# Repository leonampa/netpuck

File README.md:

# **NetPuck 5G: A Specialized 5GHz Wireless & Network Auditor**

----------

# 🗃️ This project has been archived.
**9th May:** It’s been 30 days since my latest ticket to Support, and over five weeks since the last human feedback. At this point, the project has shifted from a fun hardware challenge into a lingering chore on my to-do list. The educational ROI has hit its limit - I’ve already learned what I came for: Fusion 360, KiCad, etc. Since the program has stalled on the administrative side, I’m officially archiving the NetPuck to clear my headspace for projects that actually move forward. 

----------

# **0\. Introduction**

The NetPuck 5G is a handheld device, purpose-built to connect the worlds of software-driven network diagnostics and hardware-focused wireless analysis.

Made on Hack Club Blueprint 🚩- [https://blueprint.hackclub.com/projects/13740](https://blueprint.hackclub.com/projects/13740)

## **0.1 Why did I build this?**

* **I needed a network auditing device.** As a beginner IT Support Technician, I have a vast variety of tools for every job, but I've been lacking tools (and knowledge) regarding networking infrastructure. I've been making do with my phone and generic, no-brand WiFi strength scanning applications on my phone, but that is just not reliable for my purpose.  
* **I wanted to learn about hardware engineering.** I've always been interested in the “guts” of the devices around me. From a very young age, with a screwdriver in hand, I started taking devices that would otherwise be trashed apart, curious to see what makes them work. A few months ago, I also bought a soldering iron, and learned the skill of soldering and desoldering. In my curious journey of hardware engineering, the next step would be designing and having a custom PCB made.  
* **I wanted something to showcase in my portfolio.** Projects and contributions are largely important factors in one's portfolio, especially at an age where they cannot work, like me. I wanted to enrich my portfolio with personal projects, and Hack Club’s blueprint was the perfect, guided opportunity for me to do so.

## **0.2 What is it made of?**

It uses:

* the Waveshare ESP32-S3 Pico, as the main processing unit for the entire device  
* a BW16, solely for Access Point scanning, thanks to its 5GHz capabilities   
* a W5500 Ethernet module, for listing details about the network it is connected to  
* a 1.8’ inch LCD module, for providing all information gathered from the aforementioned boards to the user  
* a low-profile 5-way digital navigation joystick, for navigating the menus of the device  
* a MH-CD42 charging and boost-up module and two Samsung 18650 batteries, for powering the device from batteries, reliably.

## **0.3 So, what does it do?**

The NetPuck 5G has two functions; Wireless Access Point strength scanning, and Wired Network details.

* Wireless Access Point strength scanning  
  * This function uses the BW16, which communicates with the ESP32 via UART to list all 2.4GHz and 5GHz Access Points within reach, and the strength of each one, measured in dBm.  
* LAN details  
  * This function detects specific details about the network the W5500 module is plugged into. Specifically: ICMP Echo to 8.8.8.8, Gateway IP (from DHCP Lease), ICMP Echo to Gateway (Confirms local LAN integrity), LLDP (Passive sniff for Link Layer Discovery Protocol packets), Reverse DNS lookup of the Gateway’s Public IP, Gateway Domain Name (from DHCP Option 15), NLA Information, Gateway MAC (ARP-resolved)

# **1\. Pinout**

Grounds not listed; all grounds connect to each other  
The Pin/As/To/For tables are read as: The Pin \[Pin\] functions as/is labeled as \[As\], and goes to pin \[To\], (and is used) for \[For\].   

## **1.1 ESP32-S3**

| Pin | As | To | For |
| :---- | :---- | :---- | :---- |
| Vbus/40 | \+5V | MH-CD42 @ 5V OUT | Powering the ESP |
| GP5/27 | LCD\_BL | LCD @ BL | Controlling the backlight |
| GP6/29 | W5500\_RST | W5500 @ RST | Resetting the W5500 |
| GP7/31 | LCD\_RST | LCD @ RST | LCD’s Resetting the LCD |
| GP8/32 | LCD\_DC | LCD @ DC | Data/Command |
| GP9/33 | W5500\_CS | W5500 @ CS | W5500’s SPI Chip Select  |
| GP10/34 | LCD\_CS | LCD @ CS | LCD’s SPI Chip Select |
| 3V3/36 | 3V3 | LCD @ VCC, W5500 @ V | Powering the LCD and W5500 |
| GP11/1 | SPI\_MOSI | LCD @ DIN, W5500 @ MO | Transferring data via SPI from the ESP32 (Master), to the LCD and W5500 (Slaves) |
| GP12/2 | SPI\_SCK | LCD @ CLK, W5500 @ SCK | Serial Clock for SPI |
| GP13/4 | SPI\_MISO | W5500 @ MI | Transferring data via SPI from the W5500 (Slave) to the ESP32 (Master) |
| GP14/5 | BW16\_EN | BW16 @ EN | BW16’s Enable Pin |
| GP17/9 | BW16\_RX | BW16 @ 7 | UART (ESP32 → BW16) |
| GP18/10 | BW16\_TX | BW16 @ 8 | UART (ESP32 ← BW16) |
| GP34/12 | MID | STICK @ MID | Joystick’s Click |
| GP35/14 | UP | STICK @ UP | Joystick’s Up |
| GP36/15 | DOWN | STICK @ DOWN | Joystick’s Down |
| GP37/16 | LEFT | STICK @ LEFT | Joystick’s Left |
| GP38/17 | RIGHT | STICK @ RIGHT | Joystick’s Right |

## **1.2 BW16**

| Pin | As | To | For |
| :---- | :---- | :---- | :---- |
| 5V | \+5V | MH-CD42 @ 5V OUT | Powering the BW16 |
| PA7/TX | BW16\_TX | ESP @ GP17/9 | UART (ESP32 ← BW16) |
| PA8/RX | BW16\_RX | ESP @ GP18/10 | UART (ESP32 → BW16) |
| EN | BW16\_EN | ESP @ GP14/5 | Enable Pin |

## **1.3 W5500**

| Pin | As | To | For |
| :---- | :---- | :---- | :---- |
| RST | W5500\_RST | ESP @ GP6/29 | Resetting the W5500 |
| CS | W5500\_CS | ESP @ GP9/34 | W5500’s SPI Chip Select  |
| V | 3V3 | ESP @ 3V3 | Powering the LCD and W5500 |
| SCK | SPI\_SCK | ESP @ GP12/2 | Serial Clock for SPI |
| MI | SPI\_MISO | ESP @ GP13/4 | Transferring data via SPI from the W5500 (Slave) to the ESP32 (Master) |
| MO | SPI\_MOSI | ESP @ GP11/1 | Transferring data via SPI from the ESP32 (Master), to theW5500 (Slave) |

## **1.4 LCD**

| Pin | As | To | For |
| :---- | :---- | :---- | :---- |
| BL  | LCD\_BL | ESP @ GP5/27 | Controlling the backlight |
| RST  | LCD\_RST | ESP @ GP7/31 | Resetting the LCD |
| DC  | LCD\_DC | ESP @ GP8/32 | LCD’s Data/Command |
| CS  | LCD\_CS | ESP @ GP10/34 | LCD’s SPI Chip Select |
| VCC  | 3V3 | ESP @ 3V3/36 | Powering the LCD |
| DIN  | SPI\_MOSI | ESP @ GP11/1 | Transferring data via SPI from the ESP32 (Master), to the LCD (Slave) |
| CLK  | SPI\_SCK | ESP @ GP12/2 | Serial Clock for SPI |

## **1.5 Joystick** 

| Pin | As | To | For |
| :---- | :---- | :---- | :---- |
| MID | MID | ESP @ GP34/12 | Joystick’s Click |
| UP | UP | ESP @ GP35/14 | Joystick’s Up |
| DOWN | DOWN | ESP @ GP36/15 | Joystick’s Down |
| LEFT | LEFT | ESP @ GP37/16 | Joystick’s Left |
| RIGHT | RIGHT | ESP @ GP38/17 | Joystick’s Right |

## **1.6 MH-CD42 Charging Module**

| Pin | As | To | For |
| :---- | :---- | :---- | :---- |
| 5V OUT | \+5V | ESP @ Vbus/40, BW16 @ 5V | Powering the ESP and BW16 |
| VIN  | VUSB | USB @ V | Powering the MH-CD42 |
| BAT | VBAT | (external batteries) | Powering the MH-CD42 |

## **1.7 USB Port**

| Pin | As | To | For |
| :---- | :---- | :---- | :---- |
| V | VUSB | VIN | Powering the MH-CD42 |

# **2\. PCB**

I used KiCad to design the PCB. Through a few struggles (as described on Journal), I landed on this design:

# **3\. Case**

I used Autodesk Fusion to make the case (as described on Journal). The enclosure is designed for field durability, featuring a 'Sandwich Mount' architecture. It utilizes M3 heat-set inserts and M3 Nylon screws, instead of Stainless Steel, to avoid signal interference.

# **4\. Bill Of Materials**

| Item | €/pcs | Qty | € Total | Link |
| :---- | ----- | ----- | ----- | :---- |
| **GRobotronics** |  |  |  |  |
| eSUN PETG+HS 1.75mm 1kg \- Solid Black | €19.90 | 1 | €19.90 | [https://grobotronics.com/esun-petghs-1-75mm-1kg-solid-black.html](https://grobotronics.com/esun-petghs-1-75mm-1kg-solid-black.html) |
| Soldering Wire Brofil 60 100g 1mm | €7.20 | 1 | €7.20 | [https://grobotronics.com/soldering-wire-brofil-60-100g-1mm.html](https://grobotronics.com/soldering-wire-brofil-60-100g-1mm.html) |
| Waveshare ESP32-S3 Pico With Pre-soldered Headers | €13.60 | 1 | €13.60 | [https://grobotronics.com/waveshare-esp32-s3-development-board.html?variation\_id=18355](https://grobotronics.com/waveshare-esp32-s3-development-board.html?variation_id=18355) |
| Battery Lithium 18650 3.6V 3400mAh \- Samsung INR18650-35E | €5.80 | 2 | €11.60 | [https://grobotronics.com/battery-lithium-18650-3.6v-3400mah-8a-samsung-inr18650-35e.html](https://grobotronics.com/battery-lithium-18650-3.6v-3400mah-8a-samsung-inr18650-35e.html) |
| Battery Holder 2x18650 \- with Wires & Switch | €1.20 | 1 | €1.20 | [https://grobotronics.com/battery-lithium-18650-3.6v-3400mah-8a-samsung-inr18650-35e.html](https://grobotronics.com/battery-lithium-18650-3.6v-3400mah-8a-samsung-inr18650-35e.html) |
| Joystick Module 5-Way | €2.60 | 1 | €2.60 | [https://grobotronics.com/5-way-joystick-module.html](https://grobotronics.com/5-way-joystick-module.html) |
| Waveshare LCD 1.8" 128×160 SPI | €11.20 | 1 | €11.20 | [https://grobotronics.com/display-1.8-128x160-lcd-module.html](https://grobotronics.com/display-1.8-128x160-lcd-module.html) |
| USB Type-C Breakout Board \- Straight Header | €0.80 | 1 | €0.80 | [https://grobotronics.com/usb-type-c-breakout-board-straight-header.html](https://grobotronics.com/usb-type-c-breakout-board-straight-header.html) |
| Pin Header 1x40 Male 2.54 mm Black | €0.10 | 1 | €0.10 | [https://grobotronics.com/pin-header-1x40-male-2.54-mm-black.html](https://grobotronics.com/pin-header-1x40-male-2.54-mm-black.html) |
| Pin Header 1x10 Female 2.54mm | €0.17 | 4 | €0.68 | [https://grobotronics.com/pin-header-1x10-female-2.54mm.html](https://grobotronics.com/pin-header-1x10-female-2.54mm.html) |
| Pin Header 1x8 Female 2.54mm | €0.10 | 3 | €0.30 | [https://grobotronics.com/pin-header-1x8-female-2.54mm.html](https://grobotronics.com/pin-header-1x8-female-2.54mm.html) |
| Arduino Long Header 8pins | €0.25 | 1 | €0.25 | [https://grobotronics.com/arduino-long-header-8pins.html](https://grobotronics.com/arduino-long-header-8pins.html) |
| Pin Header Female 1x6 2.54mm | €0.08 | 3 | €0.24 | [https://grobotronics.com/pin-header-1x6-female-2.54mm.html](https://grobotronics.com/pin-header-1x6-female-2.54mm.html) |
| Pin Header 1x4 Long Stackable | €0.20 | 1 | €0.20 | [https://grobotronics.com/pin-header-1x4-long-stackable.html](https://grobotronics.com/pin-header-1x4-long-stackable.html) |
| Threaded Insert M3 \- 5.7x4.6mm | €0.15 | 10 | €1.50 | [https://grobotronics.com/threaded-insert-m3-short-3x4-6.html](https://grobotronics.com/threaded-insert-m3-short-3x4-6.html) |
| Bolt M3 \- Nylon (20mm) | €0.30 | 10 | €3.00 | [https://grobotronics.com/m3.html?variation\_id=12363](https://grobotronics.com/m3.html?variation_id=12363) |
| High Temperature Adhesive Tape 50mm \- 33m | €7.90 | 1 | €7.90 | [https://grobotronics.com/high-temperature-adhesive-tape-50mm-33m.html](https://grobotronics.com/high-temperature-adhesive-tape-50mm-33m.html) |
| YATO YT-2081 Side Cutting Pliers 115mm | €3.60 | 1 | €3.60 | [https://grobotronics.com/yato-cutting-pliers-115mm.html](https://grobotronics.com/yato-cutting-pliers-115mm.html) |
| Shipping (BOXNOW) | €0.00 | 0 | €0.00 |  |
| **Subtotal** |  | 44 | €85.87 |  |
|  |  |  |  |  |
| **AliExpress** |  |  |  |  |
| Dual-band WiFi \+ Bluetooth 5.0 IoT Core Board (BW16 RTL8720DN) Suitable for Arduino and Smart Home Projects (IPEX Antenna) | €7.24 | 1 | €9.52 | [https://www.aliexpress.com/item/1005010064459718.html?spm=a2g0o.detail.0.0.7236U0QJU0QJSg\&mp=1\&pdp\_npi=6%40dis%21EUR%21EUR%209.55%21EUR%201.95%21%21EUR%201.95%21%21%21%402103835e17741877141951141e5be7%2112000051007214201%21ct%21GR%21-1%21%211%210%21](https://www.aliexpress.com/item/1005010064459718.html?spm=a2g0o.detail.0.0.7236U0QJU0QJSg&mp=1&pdp_npi=6%40dis%21EUR%21EUR%209.55%21EUR%201.95%21%21EUR%201.95%21%21%21%402103835e17741877141951141e5be7%2112000051007214201%21ct%21GR%21-1%21%211%210%21) |
| 1PCS W5500 Module TCP/IP Ethernet Module Compatible with WIZ820io Network Interface RC5 IoT for Arduino | €3.91 | 1 | €4.54 | [https://www.aliexpress.com/item/1005004679288698.html?spm=a2g0o.detail.0.0.7236U0QJU0QJSg\&mp=1\&pdp\_npi=6%40dis%21EUR%21EUR%204.54%21EUR%200.88%21%21EUR%200.88%21%21%21%402103835e17741877141951141e5be7%2112000030074096066%21ct%21GR%21-1%21%211%210%21](https://www.aliexpress.com/item/1005004679288698.html?spm=a2g0o.detail.0.0.7236U0QJU0QJSg&mp=1&pdp_npi=6%40dis%21EUR%21EUR%204.54%21EUR%200.88%21%21EUR%200.88%21%21%21%402103835e17741877141951141e5be7%2112000030074096066%21ct%21GR%21-1%21%211%210%21) |
| 5/10pcs DC 5V 2A Mobile Power Diy Board 4.2V Charge/Discharge(boost)/battery protection/indicator module 3.7V lithium 18650 (MH-CD42) | €2.71 | 1 | €3.13 | [https://www.aliexpress.com/item/1005007432099008.html?spm=a2g0o.productlist.main.1.6d655d0d201MlN\&algo\_pvid=0b38d990-1f78-4ed4-ab89-ce53223c6fe6\&algo\_exp\_id=0b38d990-1f78-4ed4-ab89-ce53223c6fe6-8\&pdp\_ext\_f=%7B%22order%22%3A%22861%22%2C%22eval%22%3A%221%22%2C%22fromPage%22%3A%22search%22%7D\&pdp\_npi=6%40dis%21EUR%213.13%212.71%21%21%213.53%213.06%21%4021039a5b17741899750876391e3fa0%2112000040730748938%21sea%21GR%216308147579%21X%211%210%21n\_tag%3A-29919%3Bd%3A73d1907e%3Bm03\_new\_user%3A-29895%3BpisId%3A5000000202472607\&curPageLogUid=w2UUTZk6Qdsr\&utparam-url=scene%3Asearch%7Cquery\_from%3A%7Cx\_object\_id%3A1005007432099008%7C\_p\_origin\_prod%3A](https://www.aliexpress.com/item/1005007432099008.html?spm=a2g0o.productlist.main.1.6d655d0d201MlN&algo_pvid=0b38d990-1f78-4ed4-ab89-ce53223c6fe6&algo_exp_id=0b38d990-1f78-4ed4-ab89-ce53223c6fe6-8&pdp_ext_f=%7B%22order%22%3A%22861%22%2C%22eval%22%3A%221%22%2C%22fromPage%22%3A%22search%22%7D&pdp_npi=6%40dis%21EUR%213.13%212.71%21%21%213.53%213.06%21%4021039a5b17741899750876391e3fa0%2112000040730748938%21sea%21GR%216308147579%21X%211%210%21n_tag%3A-29919%3Bd%3A73d1907e%3Bm03_new_user%3A-29895%3BpisId%3A5000000202472607&curPageLogUid=w2UUTZk6Qdsr&utparam-url=scene%3Asearch%7Cquery_from%3A%7Cx_object_id%3A1005007432099008%7C_p_origin_prod%3A) |
| Shipping (AliExpress Choice) | €0.00 | 0 | €0.00 |  |
| **Subtotal** |  | 3 | €17.19 |  |
|  |  |  |  |  |
| **JLCPCB** |  |  |  |  |
| PCB (2 layers) | €7.43 | 1 | €7.43 |  |
| Shipping (Global Standard Direct Line) | €7.75 | 1 | €7.75 |  |
| New User Discount | \-€5.19 | 1 | \-€5.19 |  |
|  |  |  | €9.99 |  |
|  |  |  |  |  |
| **TOTAL** |  |  | €113.05 |  |
| **Conversion to USD (rate from Google Finance, €1 \=** | $1.154 |  | $130.49 |  |

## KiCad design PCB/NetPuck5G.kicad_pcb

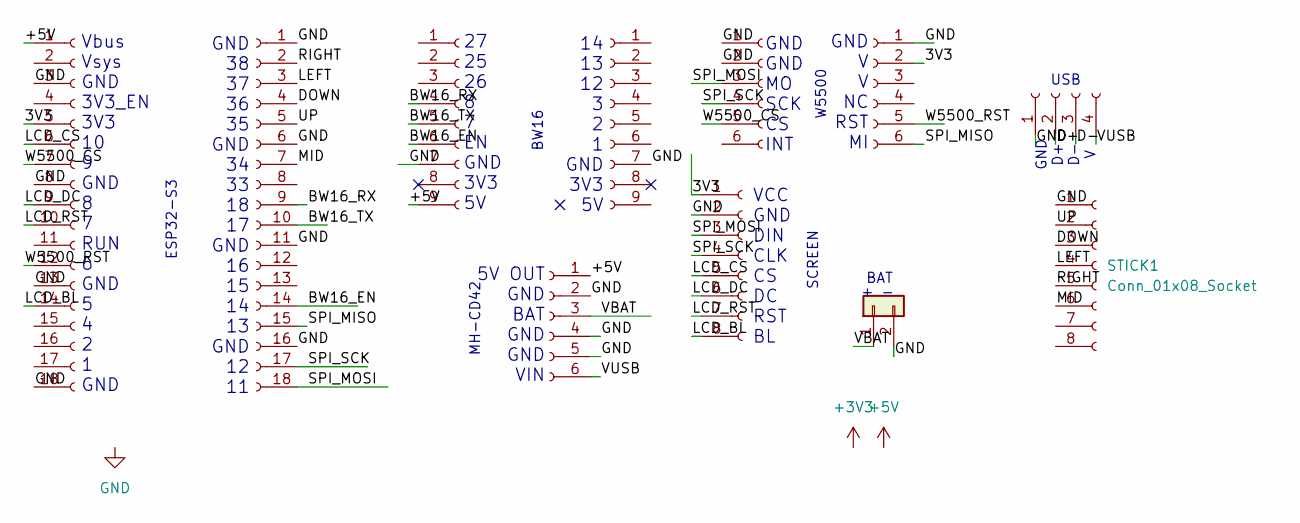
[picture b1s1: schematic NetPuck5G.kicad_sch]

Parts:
BTR1: Conn_01x02
BW-16_L1, BW-16_R1: Conn_01x09_Socket
ESP_L1: ESP_L
ESP_R1: Conn_01x18_Socket
ETH_L1: Conn_01x06_Socket
ETH_R1: Conn_01x06_Socket
MH-CD42: Conn_01x06_Socket
SCR1: Conn_01x08_Socket
STICK1: Conn_01x08_Socket
USB1: Conn_01x04_Socket

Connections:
+5V: BW-16_L1.9, ESP_L1.1, MH-CD42.1
/3V3: ESP_L1.5, ETH_R1.2, SCR1.1
/BW16_EN: BW-16_L1.6, ESP_R1.14
/BW16_RX: BW-16_L1.4, ESP_R1.9
/BW16_TX: BW-16_L1.5, ESP_R1.10
/D+: USB1.2
/D-: USB1.3
/DOWN: ESP_R1.4, STICK1.3
/LCD_BL: ESP_L1.14, SCR1.8
/LCD_CS: ESP_L1.6, SCR1.5
/LCD_DC: ESP_L1.9, SCR1.6
/LCD_RST: ESP_L1.10, SCR1.7
/LEFT: ESP_R1.3, STICK1.4
/MID: ESP_R1.7, STICK1.6
/RIGHT: ESP_R1.2, STICK1.5
/SPI_MISO: ESP_R1.15, ETH_R1.6
/SPI_MOSI: ESP_R1.18, ETH_L1.3, SCR1.3
/SPI_SCK: ESP_R1.17, ETH_L1.4, SCR1.4
/UP: ESP_R1.5, STICK1.2
/VBAT: BTR1.1, MH-CD42.3
/VUSB: MH-CD42.6, USB1.4
/W5500_CS: ESP_L1.7, ETH_L1.5
/W5500_RST: ESP_L1.12, ETH_R1.5
GND: BTR1.2, BW-16_L1.7, BW-16_R1.7, ESP_L1.3, ESP_L1.8, ESP_L1.13, ESP_L1.18, ESP_R1.1, ESP_R1.6, ESP_R1.11, ESP_R1.16, ETH_L1.1, ETH_L1.2, ETH_R1.1, MH-CD42.2, MH-CD42.4, MH-CD42.5, SCR1.2, STICK1.1, USB1.1

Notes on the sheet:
BAT
GND 38 37 36 35 GND 34 33 18 17 GND 16 15 14 13 GND 12 11
GND V V NC RST MI
14 13 12 3 2 1 GND 3V3 5V
Vbus Vsys GND 3V3_EN 3V3 10 9 GND 8 7 RUN 6 GND 5 4 2 1 GND
5V OUT GND BAT GND GND VIN
GND D+ D- V
USB
VCC GND DIN CLK CS DC RST BL
GND GND MO SCK CS INT
+ -
MH-CD42
W5500
SCREEN
27 25 26 8 7 EN GND 3V3 5V
ESP32-S3
BW16

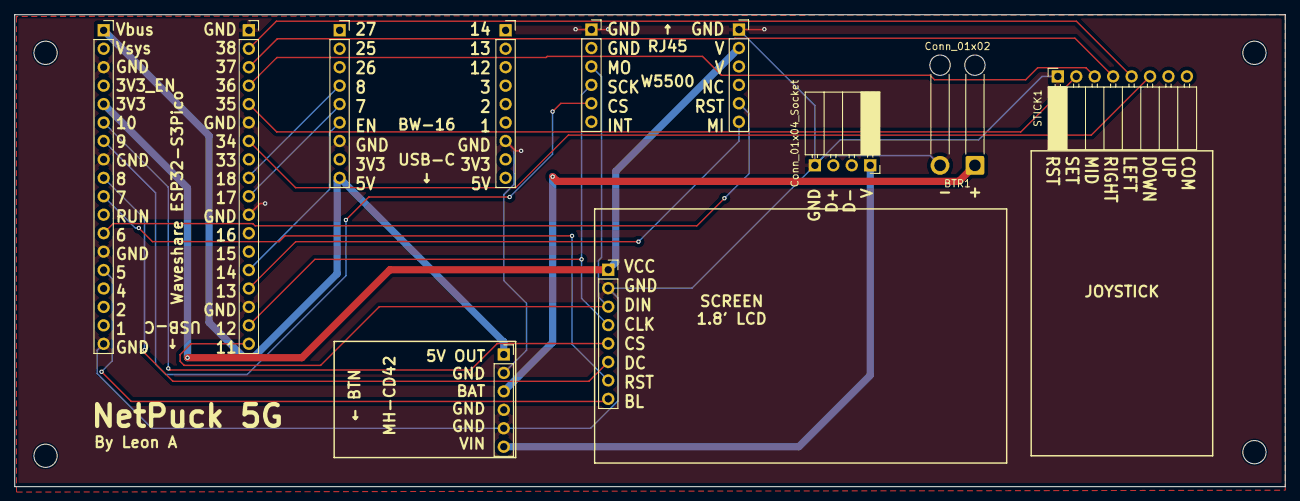
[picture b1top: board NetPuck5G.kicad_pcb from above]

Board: 2 copper layers, 175.0 x 65.0 mm, 14 parts (0 on the bottom side), 22 nets.

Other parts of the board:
BotLeft: MountingHole_3.2mm_M3
BotRight: MountingHole_3.2mm_M3
TopLeft: MountingHole_3.2mm_M3

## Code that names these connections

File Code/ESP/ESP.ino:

/* NetPuck 5G - Core Firmware (ESP32-S3) */

#include <SPI.h>
#include <Adafruit_GFX.h>
#include <Adafruit_ST7735.h>

// --- DISPLAY PINS (ST7735) ---
#define TFT_MOSI  11  // GP11
#define TFT_SCLK  12  // GP12
#define TFT_CS    10  // GP10
#define TFT_DC     8  // GP8
#define TFT_RST    7  // GP7
#define TFT_BL     5  // GP5 (Backlight Control)

// --- W5500 ETHERNET PINS ---
#define W5500_CS   9  // GP9
#define W5500_RST  6  // GP6
#define SPI_MISO  13  // GP13

// --- DIGITAL JOYSTICK PINS ---
#define JOY_MID   34  // GP34
#define JOY_UP    35  // GP35
#define JOY_DOWN  36  // GP36
#define JOY_LEFT  37  // GP37
#define JOY_RIGHT 38  // GP38

// --- BW16 5GHz MODULE PINS ---
#define BW16_EN   14  // GP14
#define BW16_RX   17  // GP17 (ESP32 TX -> BW16 RX)
#define BW16_TX   18  // GP18 (ESP32 RX <- BW16 TX)

// --- UI SETTINGS ---
#define COLOR_BG      0x0000 
#define COLOR_TEXT    0xFFFF 
#define COLOR_ACCENT  0x07E0 

Adafruit_ST7735 tft = Adafruit_ST7735(TFT_CS, TFT_DC, TFT_MOSI, TFT_SCLK, TFT_RST);

// --- APP STATES ---
enum State { MENU, SCANNING, RESULTS };
State currentState = MENU;

// --- MENU VARIABLES ---
int currentIdx = 0;
const int MAX_ITEMS = 4;
String menuItems[MAX_ITEMS] = {"5GHz SCANNER", "ETHERNET DIAG", "PACKET SNIFFER", "SETTINGS"};
bool redraw = true;

// --- SCAN VARIABLES ---
String scanSSID[8];
String scanRSSI[8];
int netCount = 0;

void setup() {
  // 1. PIN MODES
  pinMode(TFT_BL, OUTPUT);
  digitalWrite(TFT_BL, HIGH); // Backlight ON

  pinMode(W5500_CS, OUTPUT);
  digitalWrite(W5500_CS, HIGH); // De-select W5500 (Crucial!)

  pinMode(BW16_EN, OUTPUT);
  digitalWrite(BW16_EN, HIGH); 

  // 2. JOYSTICK
  pinMode(JOY_UP, INPUT_PULLUP);
  pinMode(JOY_DOWN, INPUT_PULLUP);
  pinMode(JOY_LEFT, INPUT_PULLUP);
  pinMode(JOY_RIGHT, INPUT_PULLUP);
  pinMode(JOY_MID, INPUT_PULLUP);

  // 3. START DISPLAY
  tft.initR(INITR_BLACKTAB);
  tft.setRotation(1);
  tft.fillScreen(COLOR_BG);
  
  // 4. START UART
  Serial1.begin(115200, SERIAL_8N1, BW16_RX, BW16_TX); 
}

void loop() {
  if (currentState == MENU) {
    handleMenu();
  } else if (currentState == SCANNING) {
    handleScanning();
  } else if (currentState == RESULTS) {
    handleResults();
  }
}

// --- LOGIC FUNCTIONS ---

void handleMenu() {
  if (redraw) {
    drawMenu();
    redraw = false;
  }
  
  if (digitalRead(JOY_UP) == LOW) {
    currentIdx = (currentIdx <= 0) ? MAX_ITEMS - 1 : currentIdx - 1;
    redraw = true; delay(150);
  }
  if (digitalRead(JOY_DOWN) == LOW) {
    currentIdx = (currentIdx >= MAX_ITEMS - 1) ? 0 : currentIdx + 1;
    redraw = true; delay(150);
  }
  if (digitalRead(JOY_MID) == LOW || digitalRead(JOY_RIGHT) == LOW) {
    if (currentIdx == 0) {
      // Start the Scanner
      currentState = SCANNING;
      tft.fillScreen(COLOR_BG);
      tft.setCursor(10, 60);
      tft.setTextColor(COLOR_ACCENT);
      tft.print("COMMANDING BW16...");
      
      netCount = 0; // Reset network list
      Serial1.println("SCAN"); // Send command to BW16
      delay(200);
    }
  }
}

void handleScanning() {
  // Wait for the BW16 to reply over Serial
  if (Serial1.available()) {
    String line = Serial1.readStringUntil('\n');
    line.trim();

    if (line == "END_SCAN" || line == "NO_NETWORKS") {
      currentState = RESULTS; // Scan finished!
      drawResultsScreen();
    } 
    else if (line.indexOf('|') > 0 && netCount < 8) {
      // Parse the incoming "SSID|RSSI" string
      int split = line.indexOf('|');
      scanSSID[netCount] = line.substring(0, split);
      scanRSSI[netCount] = line.substring(split + 1);
      netCount++;
      
      // Update screen so the user knows it's working
      tft.fillRect(0, 80, 160, 10, COLOR_BG);
      tft.setCursor(10, 80);
      tft.setTextColor(COLOR_TEXT);
      tft.print("Found: " + scanSSID[netCount-1]);
    }
  }
}

void handleResults() {
  // Pressing LEFT goes back to the main menu
  if (digitalRead(JOY_LEFT) == LOW || digitalRead(JOY_MID) == LOW) {
    currentState = MENU;
    redraw = true;
    delay(200);
  }
}

// --- UI DRAWING FUNCTIONS ---

void drawMenu() {
  tft.fillScreen(COLOR_BG);
  tft.fillRect(0, 0, 160, 16, COLOR_ACCENT);
  tft.setTextColor(COLOR_BG);
  tft.setCursor(4, 4);
  tft.print("NETPUCK 5G | READY");

  for (int i = 0; i < MAX_ITEMS; i++) {
    int y = 30 + (i * 18);
    if (i == currentIdx) {
      tft.fillRect(0, y - 4, 160, 16, 0x18C3);
      tft.setTextColor(COLOR_ACCENT);
      tft.setCursor(5, y);
      tft.print("> " + menuItems[i]);
    } else {
      tft.setTextColor(COLOR_TEXT);
      tft.setCursor(15, y);
      tft.print(menuItems[i]);
    }
  }
}

void drawResultsScreen() {
  tft.fillScreen(COLOR_BG);
  tft.fillRect(0, 0, 160, 16, COLOR_ACCENT);
  tft.setTextColor(COLOR_BG);
  tft.setCursor(4, 4);
  tft.print("5GHz NETWORKS FOUND");

  tft.setTextColor(COLOR_TEXT);
  if (netCount == 0) {
    tft.setCursor(10, 40);
    tft.print("No networks found.");
  } else {
    for (int i = 0; i < netCount; i++) {
      int y = 25 + (i * 12);
      // Print SSID on left, RSSI (signal strength) on right
      tft.setCursor(2, y);
      tft.print(scanSSID[i].substring(0, 15)); // Trim long names
      tft.setCursor(120, y);
      tft.print(scanRSSI[i] + "dB");
    }
  }
  
  tft.setTextColor(0x18C3); // Dim grey
  tft.setCursor(2, 115);
  tft.print("< Press LEFT to exit");
}

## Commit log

2026-03-26 Revise pricing and totals in README.md
2026-05-09 Archive NetPuck 5G project
    Archived the NetPuck 5G project due to lack of support and progress.
